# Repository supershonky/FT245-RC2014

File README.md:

# FT245-RC2014
An add-on board for the RC2014 bus using the FT245 as an ACIA/UART replacement

Files are Kicad 9 format.

The FT245 is a USB-FIFO IC. That is, it appears to be a COM port at the PC, but it has a bidirectional tristate data bus, read and write enables, and a couple of status lines. With minimal logic it can be interfaced to an 8 bit micro to provide power and a serial connection that requires no configuration at either end. Fed up of trying to work out what serial port settings to use? This doesn't care. Use any baud rate you like, the chip will still transfer at 12Mbps. Sick of trying to get weird UARTs to work in assembly language? Fear not, simply check the status "register" at BASE+0x00, and then write to, or read from BASE+0x01. It doesn't get easier!

This version is compatible with the RC2014 standard (and enhanced) bus, and appears as a MC6850. Sort of. SCM and BASIC do not use interrupts, so seem to work fine. CP/M needs an interrupt on receive, but the FT245 doesn't provide an interrupt, so the logic fakes one. It's enough to get CP/M up and running, but because there is no flow control logic, transmit delays may still be needed for some applications. With a 1ms character delay, using download to transfer packages was still faster than the SIO provided as part of the RC2014 Pro kit.

This is provided as-is, use at your own risk, I do not accept any responsibility for damages however caused.

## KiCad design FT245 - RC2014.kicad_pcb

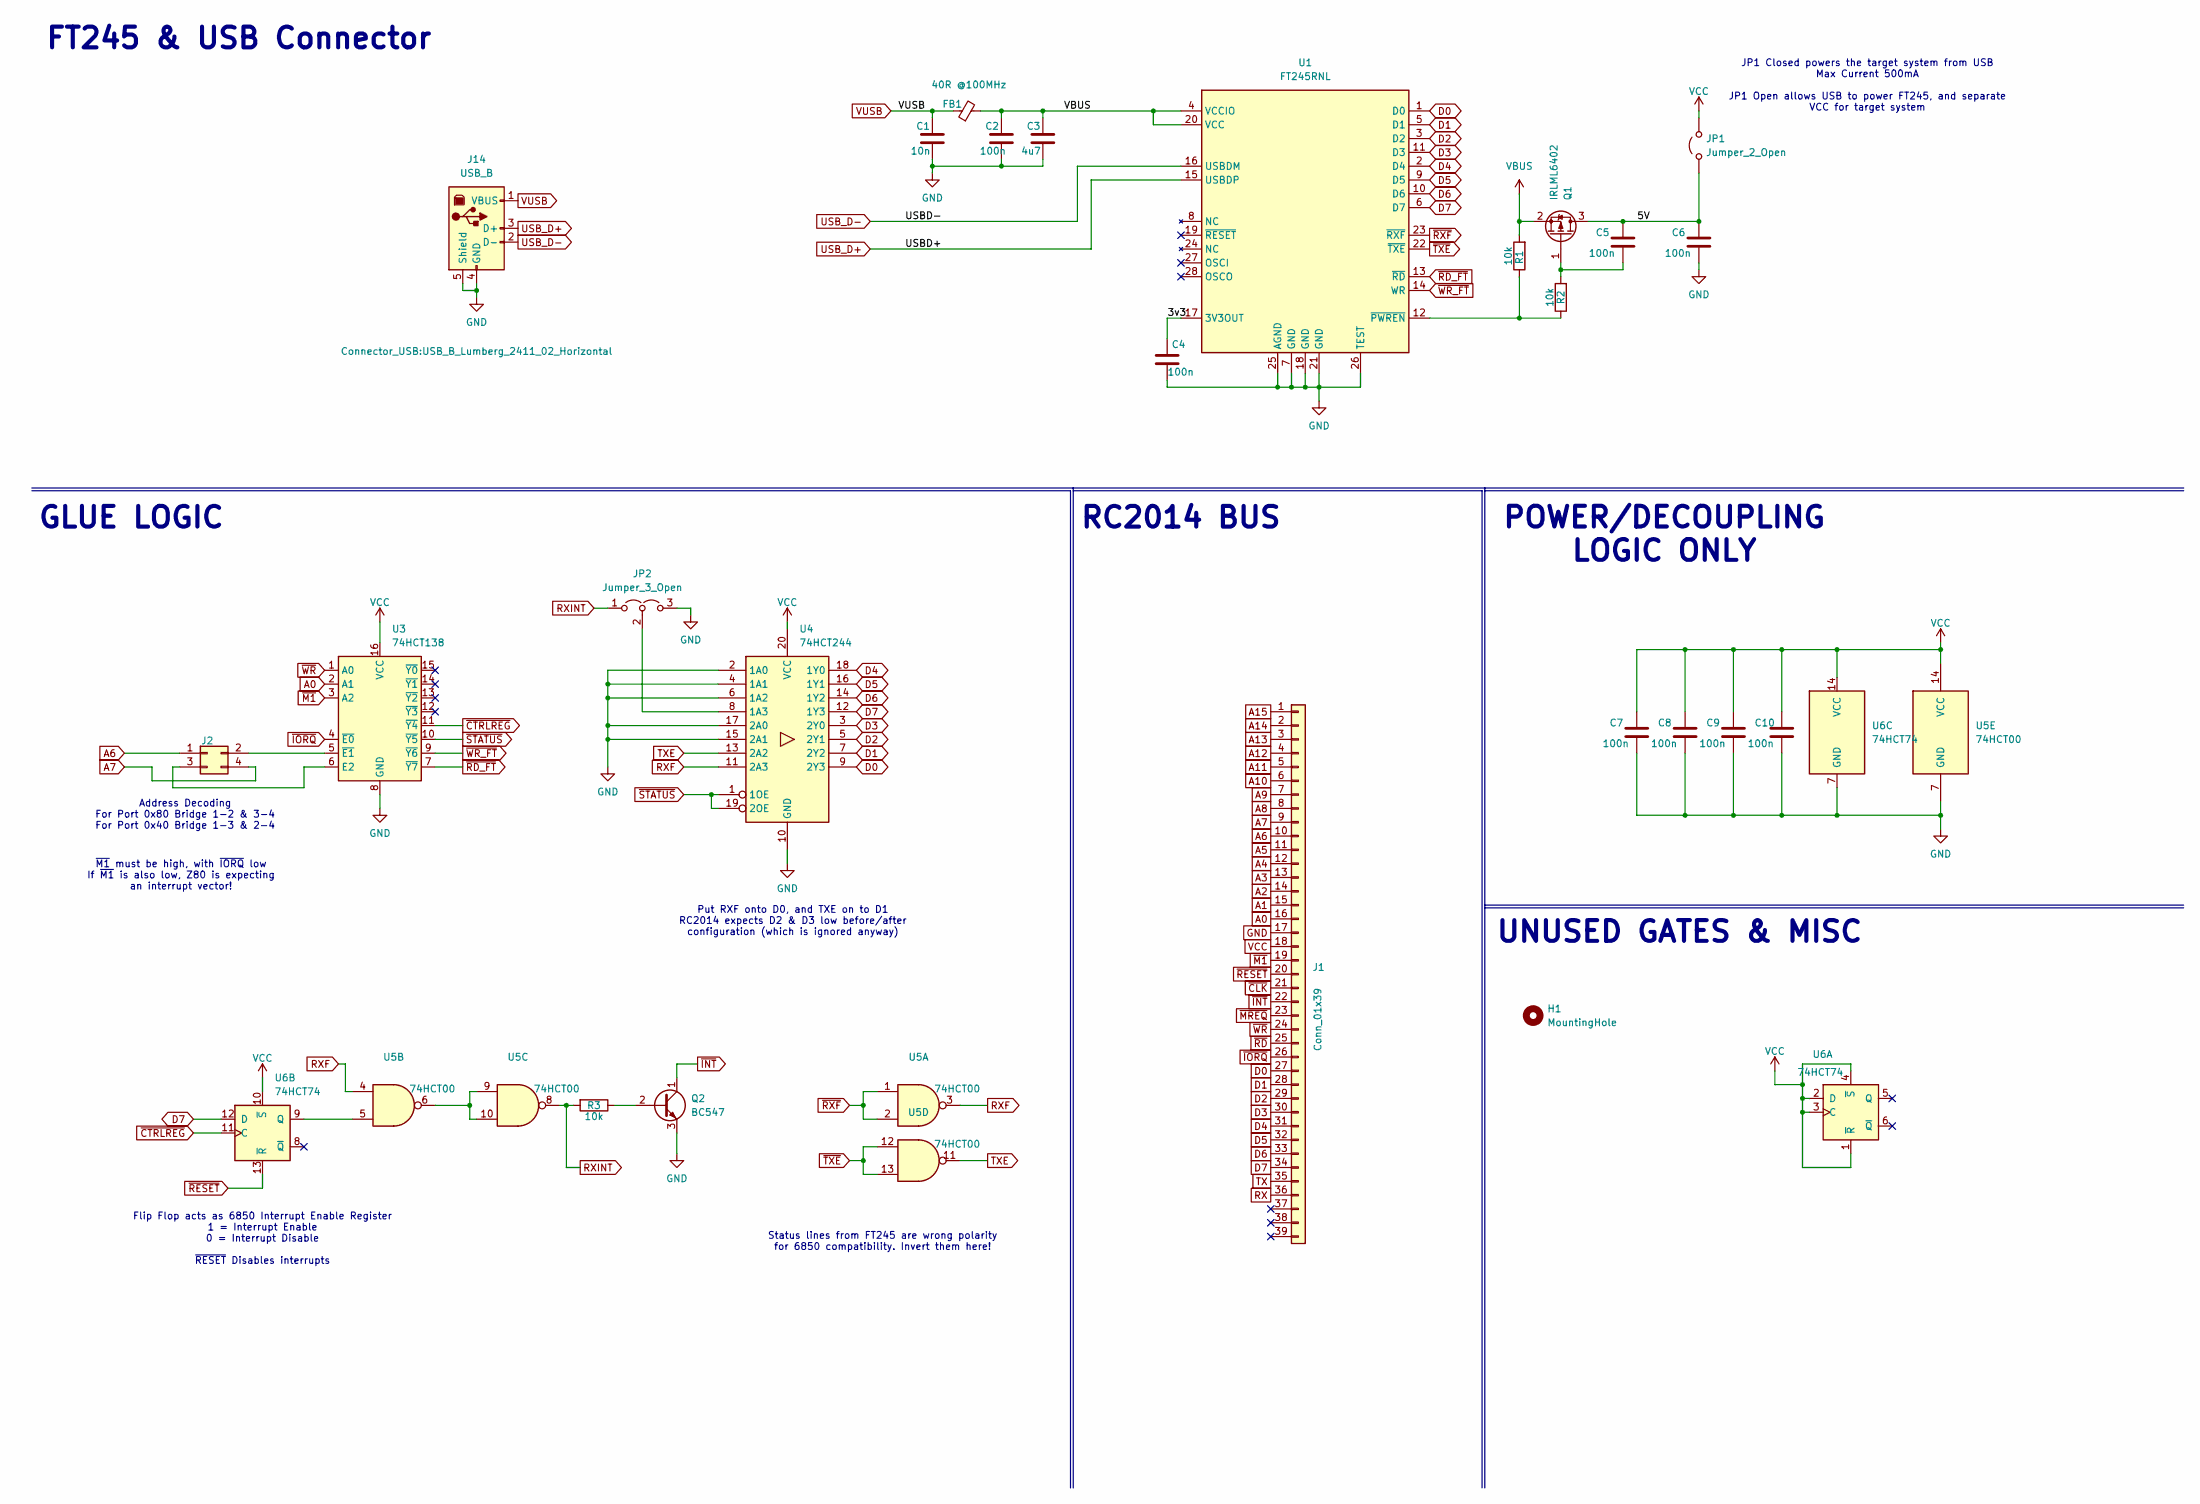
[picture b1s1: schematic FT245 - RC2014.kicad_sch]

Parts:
C1: 10n; C_0603_1608Metric_Pad1.08x0.95mm_HandSolder; LCSC C1524
C2, C4, C5, C6: 100n; C_0603_1608Metric_Pad1.08x0.95mm_HandSolder; LCSC C1525
C3: 4u7; C_0603_1608Metric_Pad1.08x0.95mm_HandSolder; LCSC C1525
C7, C8, C9, C10: 100n; C_Rect_L4.0mm_W2.5mm_P2.50mm; LCSC C1525
FB1: 40R @100MHz; C_0805_2012Metric; LCSC C369522
H1: MountingHole; MountingHole_3.2mm_M3
J1: Conn_01x39; PinHeader_1x39_P2.54mm_Vertical
J2: Conn_02x02_Odd_Even; PinHeader_2x02_P2.54mm_Vertical
J14: USB_B; USB_B_Lumberg_2411_02_Horizontal
JP1: Jumper_2_Open; PinHeader_1x02_P2.54mm_Vertical
JP2: Jumper_3_Open; SolderJumper-3_P1.3mm_Open_RoundedPad1.0x1.5mm
Q1: IRLML6402; SOT-23; LCSC C5182043
Q2: BC547; TO-92_Wide
R1, R2: 10k; R_0603_1608Metric_Pad0.98x0.95mm_HandSolder; LCSC C25744
R3: 10k; R_Axial_DIN0204_L3.6mm_D1.6mm_P7.62mm_Horizontal; LCSC C25744
U1: FT245RNL; SSOP-28_5.3x10.2mm_P0.65mm; LCSC DNF
U3: 74HCT138; DIP-16_W7.62mm
U4: 74HCT244; DIP-20_W7.62mm
U5: 74HCT00; DIP-14_W7.62mm
U6: 74HCT74; DIP-14_W7.62mm

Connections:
/3v3: C4.1, U1.17 (3V3OUT)
/5V: C5.1, C6.1, JP1.1 (A), Q1.3 (D)
A0: J1.16, U3.2 (A1)
A1: J1.15
A2: J1.14
A3: J1.13
A4: J1.12
A5: J1.11
A6: J1.10, J2.1
A7: J1.9, J2.4
A8: J1.8
A9: J1.7
A10: J1.6
A11: J1.5
A12: J1.4
A13: J1.3
A14: J1.2
A15: J1.1
D0: J1.27, U1.1 (D0), U4.9 (2Y3)
D1: J1.28, U1.5 (D1), U4.7 (2Y2)
D2: J1.29, U1.3 (D2), U4.5 (2Y1)
D3: J1.30, U1.11 (D3), U4.3 (2Y0)
D4: J1.31, U1.2 (D4), U4.18 (1Y0)
D5: J1.32, U1.9 (D5), U4.16 (1Y1)
D6: J1.33, U1.10 (D6), U4.14 (1Y2)
D7: J1.34, U1.6 (D7), U4.12 (1Y3), U6.12 (D)
GND: C1.2, C2.2, C3.2, C4.2, C6.2, C7.2, C8.2, C9.2, C10.2, J1.17, J14.4 (GND), J14.5 (Shield), JP2.3 (B), Q2.3 (E), U1.7 (GND), U1.18 (GND), U1.21 (GND), U1.25 (AGND), U1.26 (TEST), U3.8 (GND), U4.2 (1A0), U4.4 (1A1), U4.6 (1A2), U4.10 (GND), U4.15 (2A1), U4.17 (2A0), U5.7 (GND), U6.7 (GND)
unnamed: J2.2, U3.5 (~E1)
unnamed: J2.3, U3.6 (E2)
unnamed: JP2.2 (C), U4.8 (1A3)
unnamed: C5.2, Q1.1 (G), R2.2
unnamed: Q2.2 (B), R3.1
unnamed: R1.1, R2.1, U1.12 (~PWREN)
unnamed: U5.6, U5.9, U5.10
unnamed: U5.5, U6.9 (Q)
RX: J1.36
RXF: U4.11 (2A3), U5.3, U5.4
RXINT: JP2.1 (A), R3.2, U5.8
TX: J1.35
TXE: U4.13 (2A2), U5.11
USB_D+: J14.3 (D+), U1.15 (USBDP)
USB_D-: J14.2 (D-), U1.16 (USBDM)
VBUS: C2.1, C3.1, FB1.2, Q1.2 (S), R1.2, U1.4 (VCCIO), U1.20 (VCC)
VCC: C7.1, C8.1, C9.1, C10.1, J1.18, JP1.2 (B), U3.16 (VCC), U4.20 (VCC), U5.14 (VCC), U6.1 (~R), U6.2 (D), U6.3 (C), U6.4 (~S), U6.10 (~S), U6.14 (VCC)
VUSB: C1.1, FB1.1, J14.1 (VBUS)
~CLK: J1.21
~CTRLREG: U3.11 (~Y4), U6.11 (C)
~INT: J1.22, Q2.1 (C)
~IORQ: J1.26, U3.4 (~E0)
~M1: J1.19, U3.3 (A2)
~MREQ: J1.23
~RD_FT: U1.13 (~RD), U3.7 (~Y7)
~RD: J1.25
~RESET: J1.20, U6.13 (~R)
~RXF: U1.23 (~RXF), U5.1, U5.2
~STATUS: U3.10 (~Y5), U4.1 (1OE), U4.19 (2OE)
~TXE: U1.22 (~TXE), U5.12, U5.13
~WR_FT: U1.14 (WR), U3.9 (~Y6)
~WR: J1.24, U3.1 (A0)

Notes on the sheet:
~{M1} must be high, with ~{IORQ} low If ~{M1} is also low, Z80 is expecting an interrupt vector!
RC2014 BUS
GLUE LOGIC
Address Decoding For Port 0x80 Bridge 1-2 & 3-4 For Port 0x40 Bridge 1-3 & 2-4
FT245 & USB Connector
Status lines from FT245 are wrong polarity for 6850 compatibility. Invert them here!
JP1 Closed powers the target system from USB Max Current 500mA JP1 Open allows USB to power FT245, and separate VCC for target system
POWER/DECOUPLING LOGIC ONLY
Flip Flop acts as 6850 Interrupt Enable Register 1 = Interrupt Enable 0 = Interrupt Disable ~{RESET} Disables interrupts
Put RXF onto D0, and TXE on to D1 RC2014 expects D2 & D3 low before/after configuration (which is ignored anyway)
UNUSED GATES & MISC

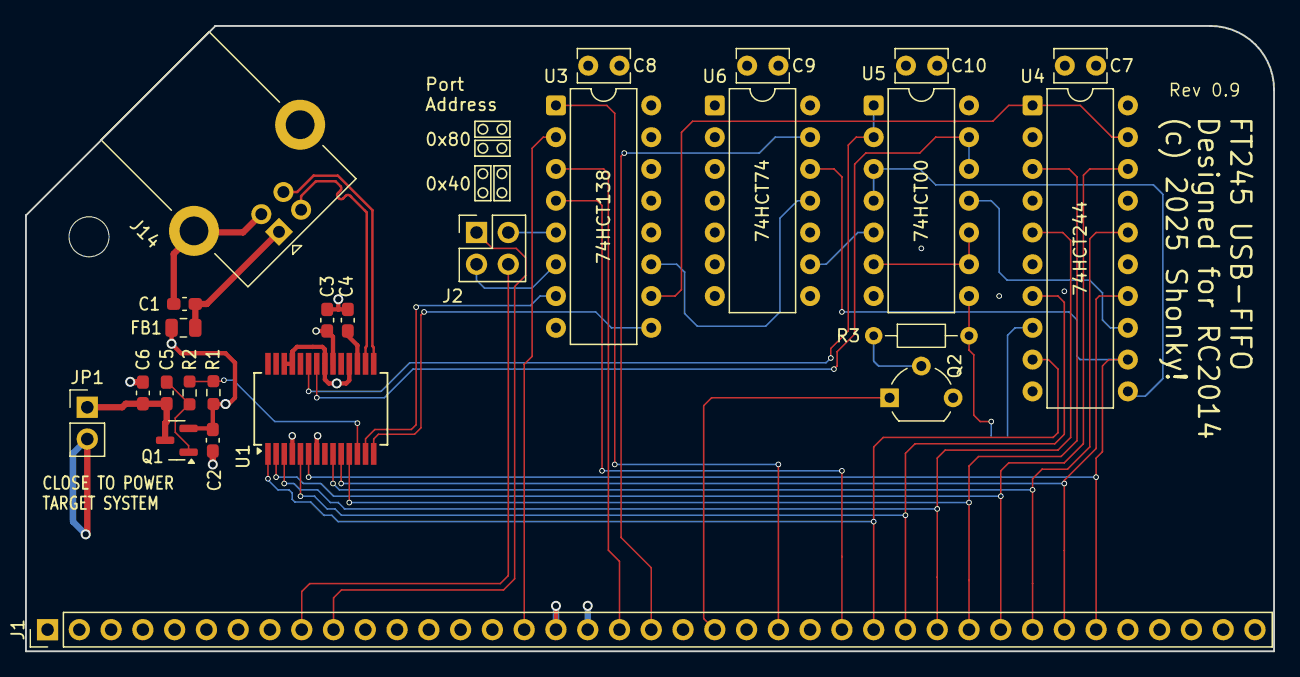
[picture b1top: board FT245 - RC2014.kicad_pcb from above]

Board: 4 copper layers, 99.8 x 50.0 mm, 27 parts (1 on the bottom side), 41 nets.

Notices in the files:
FT245 - RC2014.kicad_pcb:
(c) 2025 Shonky!
